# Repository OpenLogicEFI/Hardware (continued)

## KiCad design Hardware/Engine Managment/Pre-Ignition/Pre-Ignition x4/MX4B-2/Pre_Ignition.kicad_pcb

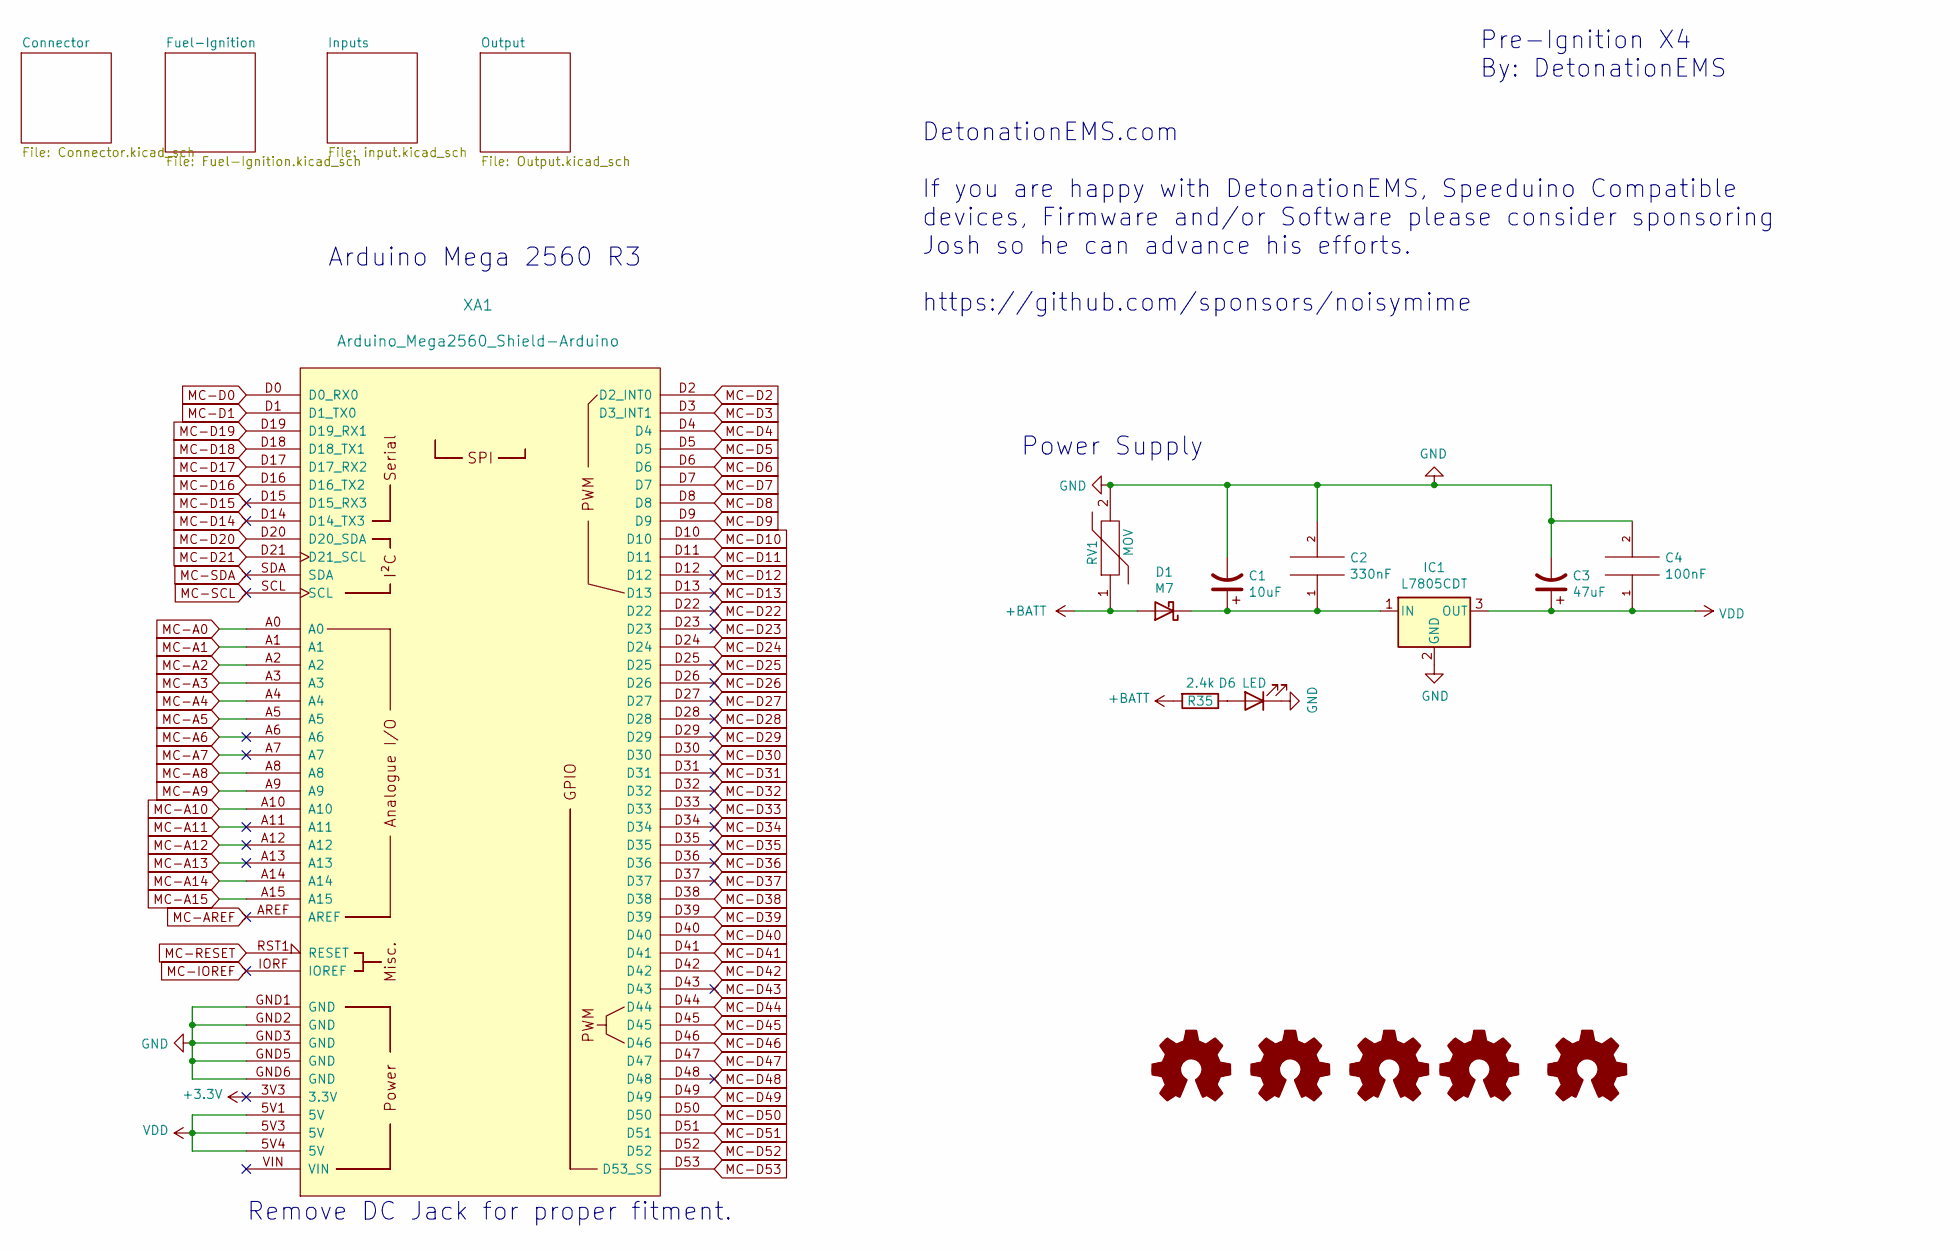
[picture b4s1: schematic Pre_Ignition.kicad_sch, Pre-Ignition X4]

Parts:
C1: 10uF; CP_Radial_Tantal_D5.0mm_P2.50mm
C2: 330nF; C_0603_1608Metric; LCSC C1615
C3: 47uF; C_1206_3216Metric; LCSC C165111
C4: 100nF; C_0603_1608Metric; LCSC C14663
D1: M7; D_SMA; LCSC C95872
D6: LED; LED_0603_1608Metric; LCSC C72043
G2: Logo_Open_Hardware_Small; TireSmoke-22mm
G3: Logo_Open_Hardware_Small; Design by DetonationEMS
G4: Logo_Open_Hardware_Small; SpeeduinoCompatible-21mm
G5: Logo_Open_Hardware_Small; Pre-IgnitionX4-30mm
G6: Logo_Open_Hardware_Small; OSHW-Logo2_14.6x12mm_SilkScreen
IC1: L7805CDT; TO-252-2-Thermal-Pad; LCSC C310413
R35: 2.4k; R_0603_1608Metric; LCSC C22940
RV1: MOV
XA1: Arduino_Mega2560_Shield-Arduino; Arduino_Mega2560_Shield_IO_Only_No_Silk_Screen

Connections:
+3V3: XA1.3V3 (3.3V)
+BATT: D1.2 (A), R35.2, RV1.1; also elsewhere on the board
Flex: XA1.D2 (D2_INT0); also elsewhere on the board
MC-A0: XA1.A0; also elsewhere on the board
MC-A1: XA1.A1; also elsewhere on the board
MC-A2: XA1.A2; also elsewhere on the board
MC-A3: XA1.A3; also elsewhere on the board
MC-A4: XA1.A4; also elsewhere on the board
MC-A5: XA1.A5; also elsewhere on the board
MC-A6: XA1.A6
MC-A7: XA1.A7
MC-A8: XA1.A8; also elsewhere on the board
MC-A9: XA1.A9; also elsewhere on the board
MC-A10: XA1.A10; also elsewhere on the board
MC-A11: XA1.A11
MC-A12: XA1.A12
MC-A13: XA1.A13
MC-A14: XA1.A14; also elsewhere on the board
MC-A15: XA1.A15; also elsewhere on the board
MC-AREF: XA1.AREF
MC-D0: XA1.D0 (D0_RX0); also elsewhere on the board
MC-D1: XA1.D1 (D1_TX0); also elsewhere on the board
MC-D3: XA1.D3 (D3_INT1)
MC-D4: XA1.D4; also elsewhere on the board
MC-D5: XA1.D5; also elsewhere on the board
MC-D6: XA1.D6; also elsewhere on the board
MC-D7: XA1.D7; also elsewhere on the board
MC-D8: XA1.D8; also elsewhere on the board
MC-D9: XA1.D9; also elsewhere on the board
MC-D10: XA1.D10; also elsewhere on the board
MC-D11: XA1.D11; also elsewhere on the board
MC-D12: XA1.D12
MC-D13: XA1.D13
MC-D14: XA1.D14 (D14_TX3)
MC-D15: XA1.D15 (D15_RX3)
MC-D16: XA1.D16 (D16_TX2); also elsewhere on the board
MC-D17: XA1.D17 (D17_RX2); also elsewhere on the board
MC-D18: XA1.D18 (D18_TX1); also elsewhere on the board
MC-D19: XA1.D19 (D19_RX1); also elsewhere on the board
MC-D20: XA1.D20 (D20_SDA); also elsewhere on the board
MC-D21: XA1.D21 (D21_SCL); also elsewhere on the board
MC-D22: XA1.D22
MC-D23: XA1.D23
MC-D24: XA1.D24; also elsewhere on the board
MC-D25: XA1.D25
MC-D26: XA1.D26
MC-D27: XA1.D27
MC-D28: XA1.D28
MC-D29: XA1.D29
MC-D30: XA1.D30
MC-D31: XA1.D31
MC-D32: XA1.D32
MC-D33: XA1.D33
MC-D34: XA1.D34
MC-D35: XA1.D35
MC-D36: XA1.D36
MC-D37: XA1.D37
MC-D38: XA1.D38; also elsewhere on the board
MC-D39: XA1.D39; also elsewhere on the board
MC-D40: XA1.D40; also elsewhere on the board
MC-D41: XA1.D41; also elsewhere on the board
MC-D42: XA1.D42; also elsewhere on the board
MC-D43: XA1.D43
MC-D44: XA1.D44; also elsewhere on the board
MC-D45: XA1.D45; also elsewhere on the board
MC-D46: XA1.D46; also elsewhere on the board
MC-D47: XA1.D47; also elsewhere on the board
MC-D48: XA1.D48
MC-D49: XA1.D49; also elsewhere on the board
MC-D50: XA1.D50; also elsewhere on the board
MC-D51: XA1.D51; also elsewhere on the board
MC-D52: XA1.D52; also elsewhere on the board
MC-D53: XA1.D53 (D53_SS); also elsewhere on the board
MC-IOREF: XA1.IORF (IOREF)
MC-RESET: XA1.RST1 (RESET); also elsewhere on the board
MC-SCL: XA1.SCL
MC-SDA: XA1.SDA
unnamed: C1.1, C2.1, D1.1 (K), IC1.1 (IN)
unnamed: D6.2 (A), R35.1

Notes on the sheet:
Remove DC Jack for proper fitment.
Pre-Ignition X4 By: DetonationEMS
DetonationEMS.com If you are happy with DetonationEMS, Speeduino Compatible devices, Firmware and/or Software please consider sponsoring Josh so he can advance his efforts. https://github.com/sponsors/noisymime
Arduino Mega 2560 R3
Power Supply

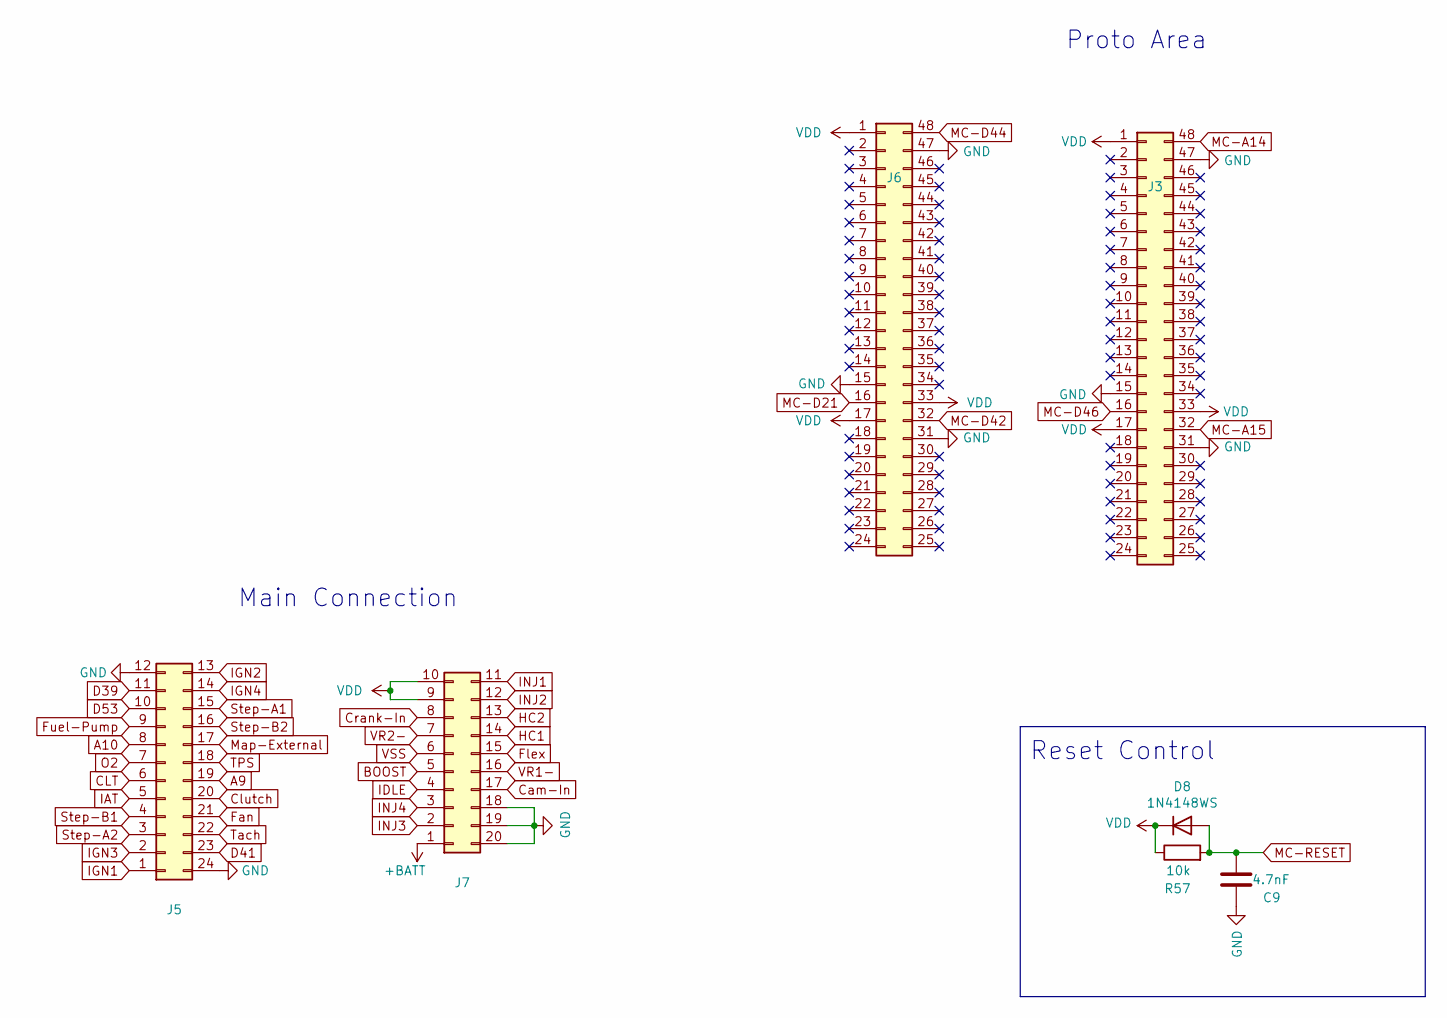
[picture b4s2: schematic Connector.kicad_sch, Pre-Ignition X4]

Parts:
C9: 4.7nF; C_0603_1608Metric; LCSC C53987
D8: 1N4148WS; D_SOD-323F; LCSC C2128
J3, J6: Conn_02x16_Counter_Clockwise; PROTO-3X16
J5: Conn_02x12_Counter_Clockwise; Molex_Micro-Fit_3.0_43045-2400_2x12_P3.00mm_Horizontal
J7: Conn_02x10_Counter_Clockwise; Molex_Micro-Fit_3.0_43045-2000_2x10_P3.00mm_Horizontal
R57: 10k; R_0603_1608Metric; LCSC C25804

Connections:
+BATT: J7.1; also elsewhere on the board
A9: J5.19; also elsewhere on the board
A10: J5.8; also elsewhere on the board
BOOST: J7.5; also elsewhere on the board
CLT: J5.6; also elsewhere on the board
Cam-In: J7.17; also elsewhere on the board
Clutch: J5.20; also elsewhere on the board
Crank-In: J7.8; also elsewhere on the board
D39: J5.11; also elsewhere on the board
D41: J5.23; also elsewhere on the board
D53: J5.10; also elsewhere on the board
Fan: J5.21; also elsewhere on the board
Flex: J7.15; also elsewhere on the board
Fuel-Pump: J5.9; also elsewhere on the board
HC1: J7.14; also elsewhere on the board
HC2: J7.13; also elsewhere on the board
IAT: J5.5; also elsewhere on the board
IDLE: J7.4; also elsewhere on the board
IGN1: J5.1; also elsewhere on the board
IGN2: J5.13; also elsewhere on the board
IGN3: J5.2; also elsewhere on the board
IGN4: J5.14; also elsewhere on the board
INJ1: J7.11; also elsewhere on the board
INJ2: J7.12; also elsewhere on the board
INJ3: J7.2; also elsewhere on the board
INJ4: J7.3; also elsewhere on the board
MC-A14: J3.48; also elsewhere on the board
MC-A15: J3.32; also elsewhere on the board
MC-D20: J7.6; also elsewhere on the board
MC-D21: J6.16; also elsewhere on the board
MC-D42: J6.32; also elsewhere on the board
MC-D44: J6.48; also elsewhere on the board
MC-D46: J3.16; also elsewhere on the board
MC-RESET: C9.2, D8.2 (A), R57.2; also elsewhere on the board
Map-External: J5.17; also elsewhere on the board
O2: J5.7; also elsewhere on the board
Step-A1: J5.15; also elsewhere on the board
Step-A2: J5.3; also elsewhere on the board
Step-B1: J5.4; also elsewhere on the board
Step-B2: J5.16; also elsewhere on the board
TPS: J5.18; also elsewhere on the board
Tach: J5.22; also elsewhere on the board
VR1-: J7.16; also elsewhere on the board
VR2-: J7.7; also elsewhere on the board

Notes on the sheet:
Reset Control
Main Connection
Proto Area

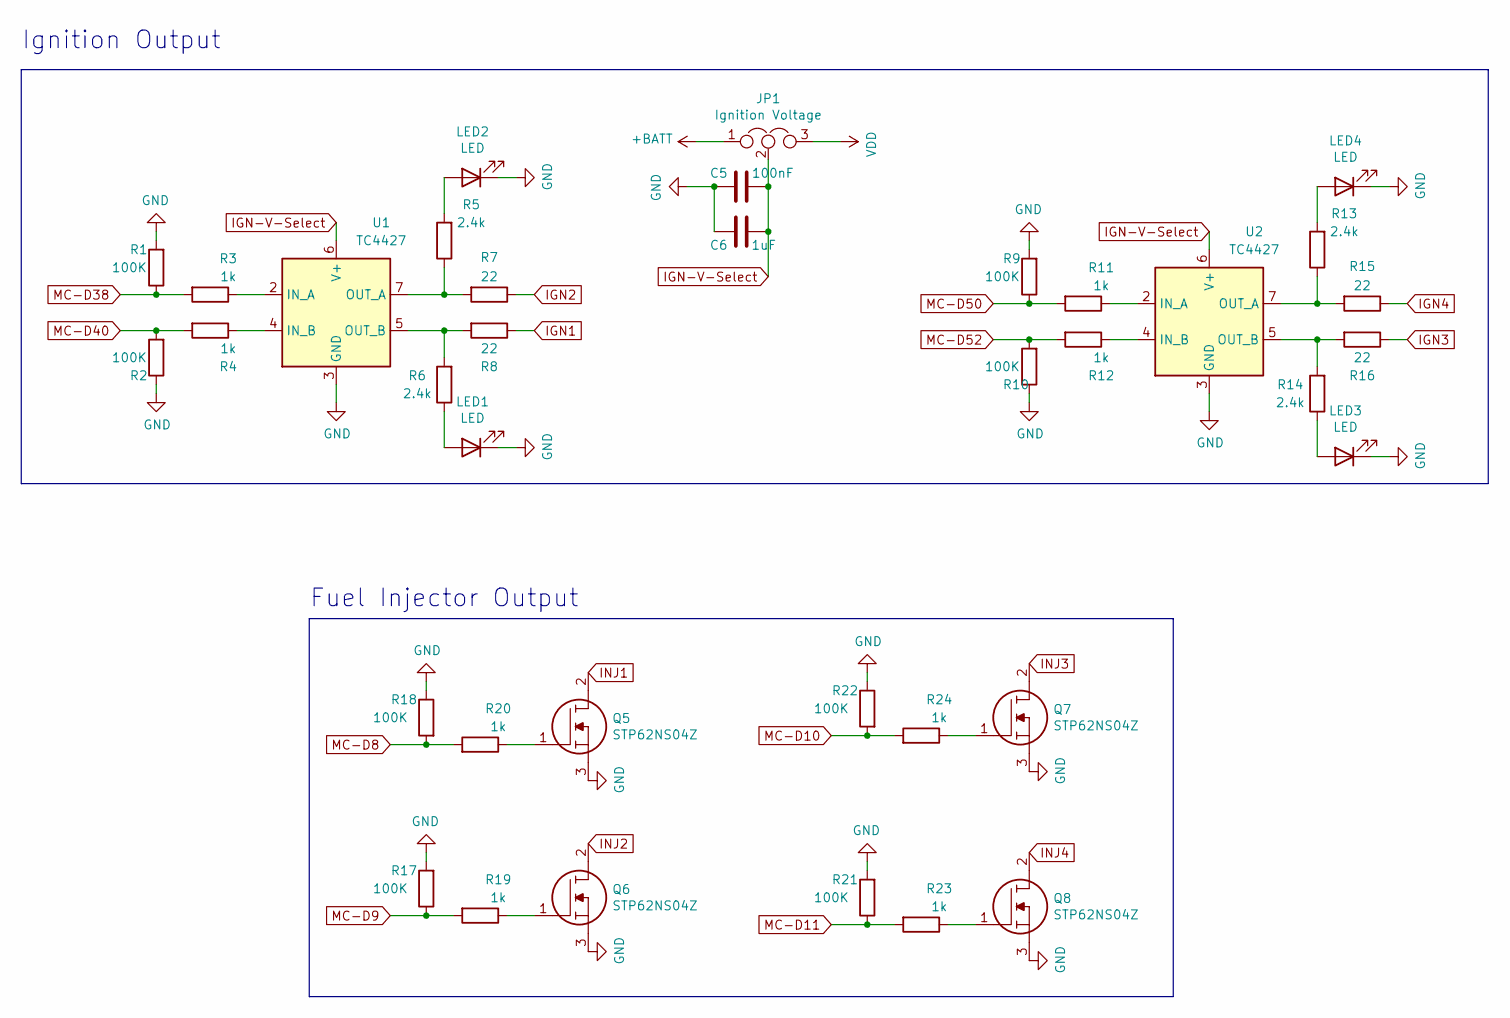
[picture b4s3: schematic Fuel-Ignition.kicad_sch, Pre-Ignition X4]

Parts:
C5: 100nF; C_0603_1608Metric; JLC C14663
C6: 1uF; C_0603_1608Metric; JLC C15849
JP1: Ignition Voltage; 3-PinSwitch
LED1, LED2, LED3, LED4: LED; LED_0603_1608Metric; JLC C2286
Q5, Q6, Q7, Q8: STP62NS04Z; TO-220-3_Vertical; Manufacturer_Part_Number STP62NS04Z; Mouser Part Number 511-STP62NS04Z
R1, R2, R9, R10, R17, R18, R21, R22: 100K; R_0603_1608Metric; JLC C25803
R3, R4, R11, R12, R19, R20, R23, R24: 1k; R_0603_1608Metric; JLC C21190
R5: 2.4k; R_0603_1608Metric; LCSC C22940
R6, R13, R14: 2.4k; R_0603_1608Metric; JLC C22940
R7, R8, R15, R16: 22; R_0805_2012Metric; JLC C17561
U1, U2: TC4427; SOIC-8_3.9x4.9mm_P1.27mm; JLC C31450

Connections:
+BATT: JP1.1; also elsewhere on the board
IGN1: R8.1; also elsewhere on the board
IGN2: R7.1; also elsewhere on the board
IGN3: R16.1; also elsewhere on the board
IGN4: R15.1; also elsewhere on the board
IGN-V-Select: C5.1, C6.1, JP1.2, U1.6 (V+), U2.6 (V+)
INJ1: Q5.2; also elsewhere on the board
INJ2: Q6.2; also elsewhere on the board
INJ3: Q7.2; also elsewhere on the board
INJ4: Q8.2; also elsewhere on the board
MC-D8: R18.2, R20.2; also elsewhere on the board
MC-D9: R17.1, R19.2; also elsewhere on the board
MC-D10: R22.2, R24.2; also elsewhere on the board
MC-D11: R21.1, R23.2; also elsewhere on the board
MC-D38: R1.1, R3.2; also elsewhere on the board
MC-D40: R2.2, R4.2; also elsewhere on the board
MC-D50: R9.1, R11.2; also elsewhere on the board
MC-D52: R10.2, R12.2; also elsewhere on the board
unnamed: LED1.2 (A), R6.1
unnamed: LED2.2 (A), R5.2
unnamed: LED3.2 (A), R14.1
unnamed: LED4.2 (A), R13.2
unnamed: Q5.1, R20.1
unnamed: Q6.1, R19.1
unnamed: Q7.1, R24.1
unnamed: Q8.1, R23.1
unnamed: R3.1, U1.2 (IN_A)
unnamed: R4.1, U1.4 (IN_B)
unnamed: R5.1, R7.2, U1.7 (OUT_A)
unnamed: R6.2, R8.2, U1.5 (OUT_B)
unnamed: R11.1, U2.2 (IN_A)
unnamed: R12.1, U2.4 (IN_B)
unnamed: R13.1, R15.2, U2.7 (OUT_A)
unnamed: R14.2, R16.2, U2.5 (OUT_B)

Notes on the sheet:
Ignition Output
Fuel Injector Output

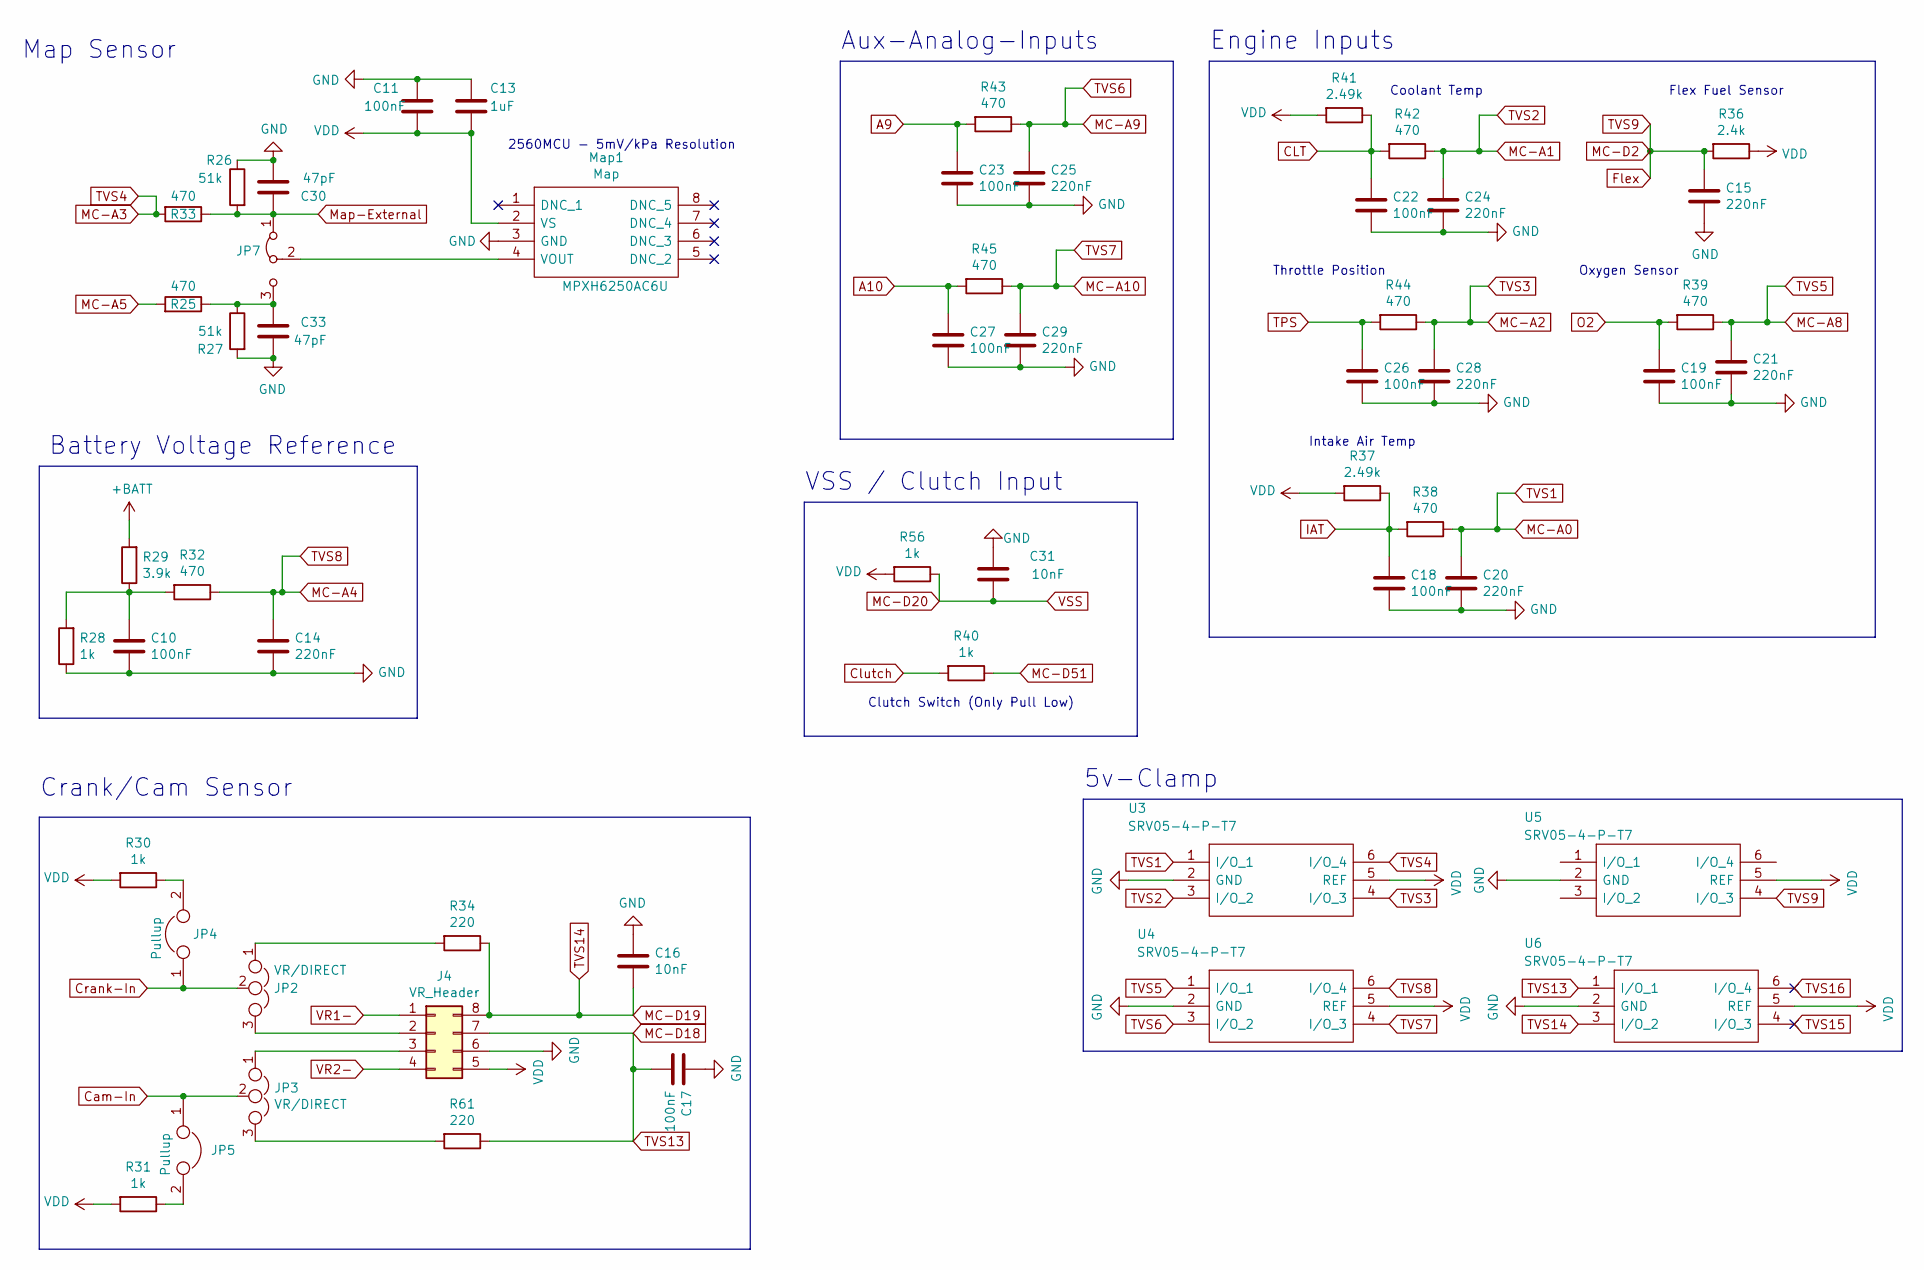
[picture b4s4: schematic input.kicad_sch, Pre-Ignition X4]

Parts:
C10, C11, C17, C18, C19, C22, C23, C26, C27: 100nF; C_0603_1608Metric; JLC C14663
C13: 1uF; C_0603_1608Metric; JLC C15849
C14, C15, C20, C21, C24, C25, C28, C29: 220nF; C_0603_1608Metric; JLC C5378
C16, C31: 10nF; C_0603_1608Metric; JLC C57112
C30, C33: 47pF; C_0603_1608Metric; LCSC C1671
J4: VR_Header; Socket_VRConditioner
JP2, JP3: VR/DIRECT; 3x1-GPIO
JP4, JP5: Pullup; 1x02-Proto
JP7: Jumper_3_Bridged12; 3-PinSwitch
Map1: Map; Freescale_98ARH99066A; Manufacturer_Part_Number MPXH6250AC6U; Mouser Part Number 841-MPXH6250AC6U
R25, R32, R33, R38, R39, R42, R43, R44, R45: 470; R_0603_1608Metric; JLC C23179
R26, R27: 51k; R_0603_1608Metric; JLC C23196
R28, R30, R31, R40, R56: 1k; R_0603_1608Metric; JLC C21190
R29: 3.9k; R_0603_1608Metric; JLC C23018
R34, R61: 220; R_0603_1608Metric; LCSC C22962
R36: 2.4k; R_0603_1608Metric; JLC C22940
R37, R41: 2.49k; R_0603_1608Metric; LCSC C491121
U3, U4, U5, U6: SRV05-4-P-T7; SOT-23-6; JLC C85364

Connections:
+BATT: R29.2; also elsewhere on the board
A9: C23.1, R43.2; also elsewhere on the board
A10: C27.1, R45.2; also elsewhere on the board
CLT: C22.1, R41.1, R42.2; also elsewhere on the board
Cam-In: JP3.2, JP5.1; also elsewhere on the board
Clutch: R40.2; also elsewhere on the board
Crank-In: JP2.2, JP4.1; also elsewhere on the board
Flex: C15.1, R36.2, U5.4 (I/O_3); also elsewhere on the board
IAT: C18.1, R37.1, R38.2; also elsewhere on the board
MC-A0: C20.1, R38.1, U3.1 (I/O_1); also elsewhere on the board
MC-A1: C24.1, R42.1, U3.3 (I/O_2); also elsewhere on the board
MC-A2: C28.1, R44.1, U3.4 (I/O_3); also elsewhere on the board
MC-A3: R33.2, U3.6 (I/O_4); also elsewhere on the board
MC-A4: C14.1, R32.1, U4.6 (I/O_4); also elsewhere on the board
MC-A5: R25.2; also elsewhere on the board
MC-A8: C21.1, R39.1, U4.1 (I/O_1); also elsewhere on the board
MC-A9: C25.1, R43.1, U4.3 (I/O_2); also elsewhere on the board
MC-A10: C29.1, R45.1, U4.4 (I/O_3); also elsewhere on the board
MC-D18: C17.2, J4.7, R61.1, U6.1 (I/O_1); also elsewhere on the board
MC-D19: C16.2, J4.8, R34.1, U6.3 (I/O_2); also elsewhere on the board
MC-D20: C31.1, R56.1; also elsewhere on the board
MC-D51: R40.1; also elsewhere on the board
Map-External: C30.1, JP7.1 (A), R26.2, R33.1; also elsewhere on the board
unnamed: C10.1, R28.2, R29.1, R32.2
unnamed: C33.1, JP7.3 (B), R25.1, R27.1
unnamed: J4.2, JP2.3
unnamed: J4.3, JP3.1
unnamed: JP2.1, R34.2
unnamed: JP3.3, R61.2
unnamed: JP4.2, R30.1
unnamed: JP5.2, R31.1
unnamed: JP7.2 (C), Map1.4 (VOUT)
O2: C19.1, R39.2; also elsewhere on the board
TPS: C26.1, R44.2; also elsewhere on the board
TVS15: U6.4 (I/O_3)
TVS16: U6.6 (I/O_4)
VR1-: J4.1; also elsewhere on the board
VR2-: J4.4; also elsewhere on the board

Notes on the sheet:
2560MCU - 5mV/kPa Resolution
Coolant Temp
Throttle Position
VSS / Clutch Input
Intake Air Temp
Battery Voltage Reference
Crank/Cam Sensor
Map Sensor
Engine Inputs
Clutch Switch (Only Pull Low)
Aux-Analog-Inputs
Flex Fuel Sensor
Oxygen Sensor
5v-Clamp

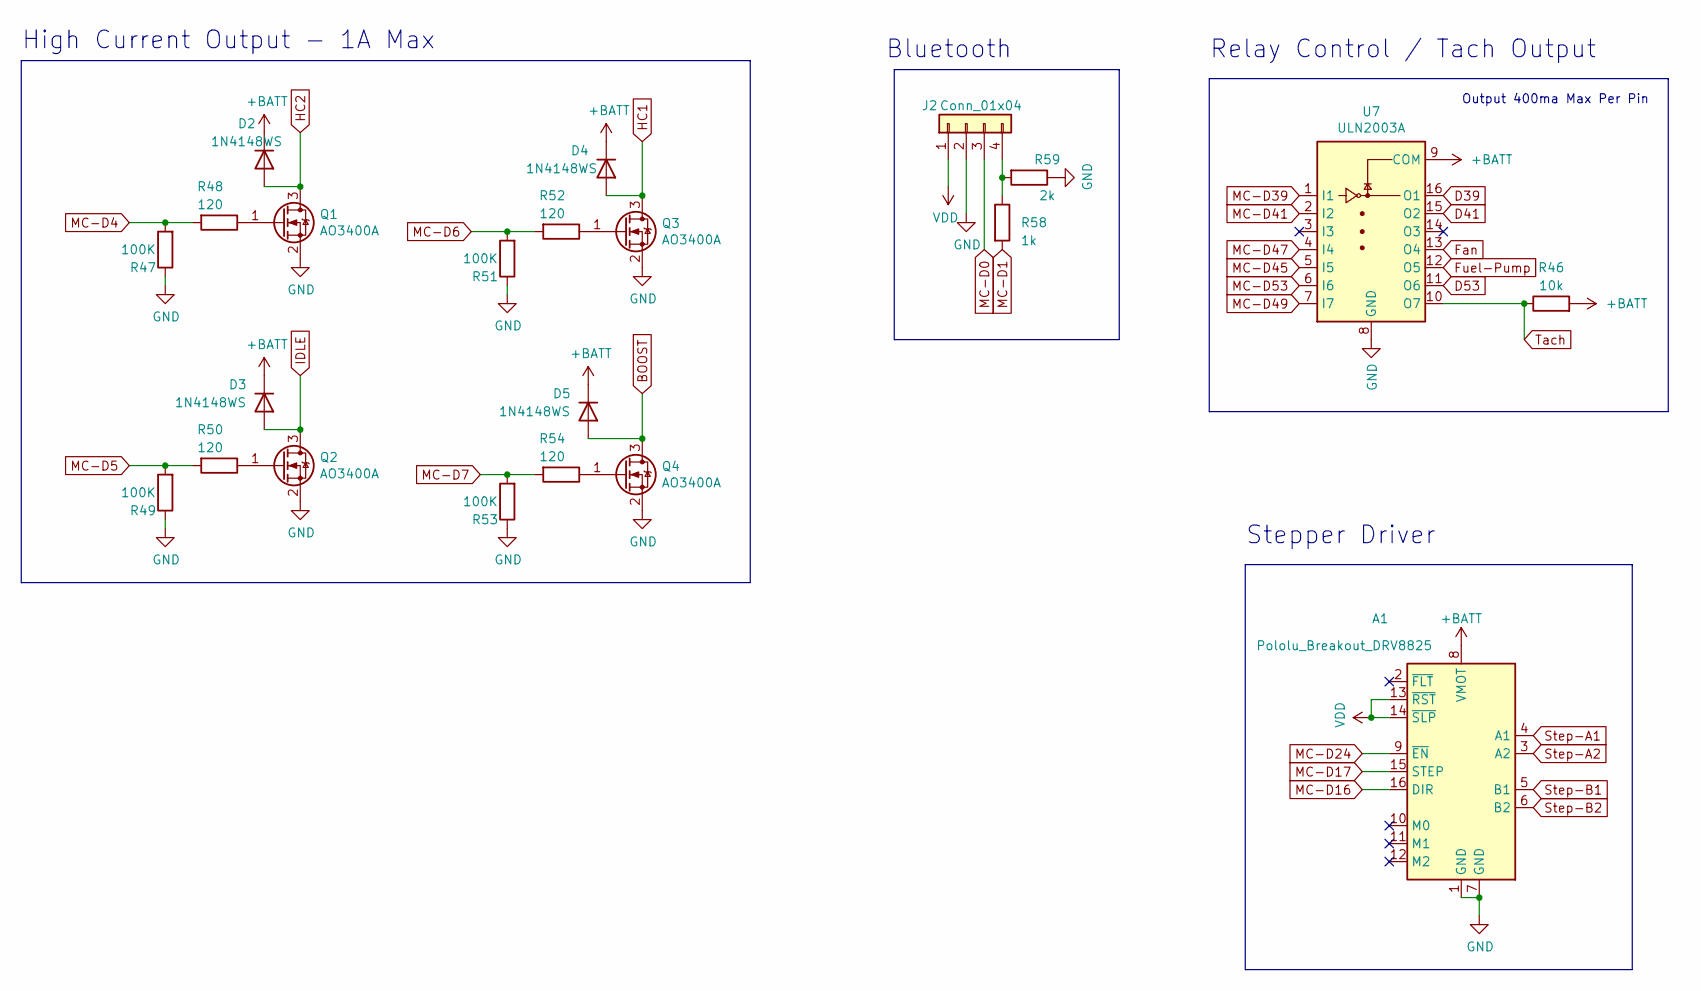
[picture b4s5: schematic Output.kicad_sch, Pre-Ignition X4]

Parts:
A1: Pololu_Breakout_DRV8825; Pololu_Breakout-16_15.2x20.3mm
D2, D3, D4, D5: 1N4148WS; D_SOD-323F; JLC C2128
J2: Conn_01x04; 1X4-PROTO
Q1, Q2, Q3, Q4: AO3400A; SOT-23; JLC C20917
R46: 10k; R_0603_1608Metric; JLC C25804
R47, R49, R51, R53: 100K; R_0603_1608Metric; LCSC C25803
R48, R50, R52, R54: 120; R_0603_1608Metric; LCSC C22787
R58: 1k; R_0603_1608Metric; LCSC C21190
R59: 2k; R_0603_1608Metric; LCSC C22975
U7: ULN2003A; SOIC-16_3.9x9.9mm_P1.27mm; JLC C7512

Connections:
+BATT: A1.8 (VMOT), D2.1 (K), D3.1 (K), D4.1 (K), D5.1 (K), R46.2, U7.9 (COM); also elsewhere on the board
BOOST: D5.2 (A), Q4.3 (D); also elsewhere on the board
D39: U7.16 (O1); also elsewhere on the board
D41: U7.15 (O2); also elsewhere on the board
D53: U7.11 (O6); also elsewhere on the board
Fan: U7.13 (O4); also elsewhere on the board
Fuel-Pump: U7.12 (O5); also elsewhere on the board
HC1: D4.2 (A), Q3.3 (D); also elsewhere on the board
HC2: D2.2 (A), Q1.3 (D); also elsewhere on the board
IDLE: D3.2 (A), Q2.3 (D); also elsewhere on the board
MC-D0: J2.3; also elsewhere on the board
MC-D1: R58.2; also elsewhere on the board
MC-D4: R47.2, R48.2; also elsewhere on the board
MC-D5: R49.2, R50.2; also elsewhere on the board
MC-D6: R51.2, R52.2; also elsewhere on the board
MC-D7: R53.2, R54.2; also elsewhere on the board
MC-D16: A1.16 (DIR); also elsewhere on the board
MC-D17: A1.15 (STEP); also elsewhere on the board
MC-D24: A1.9 (~EN); also elsewhere on the board
MC-D39: U7.1 (I1); also elsewhere on the board
MC-D41: U7.2 (I2); also elsewhere on the board
MC-D45: U7.5 (I5); also elsewhere on the board
MC-D47: U7.4 (I4); also elsewhere on the board
MC-D49: U7.7 (I7); also elsewhere on the board
MC-D53: U7.6 (I6); also elsewhere on the board
unnamed: J2.4, R58.1, R59.2
unnamed: Q1.1 (G), R48.1
unnamed: Q2.1 (G), R50.1
unnamed: Q3.1 (G), R52.1
unnamed: Q4.1 (G), R54.1
Step-A1: A1.4 (A1); also elsewhere on the board
Step-A2: A1.3 (A2); also elsewhere on the board
Step-B1: A1.5 (B1); also elsewhere on the board
Step-B2: A1.6 (B2); also elsewhere on the board
Tach: R46.1, U7.10 (O7); also elsewhere on the board

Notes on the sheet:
Bluetooth
High Current Output - 1A Max
Relay Control / Tach Output
Stepper Driver
Output 400ma Max Per Pin

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
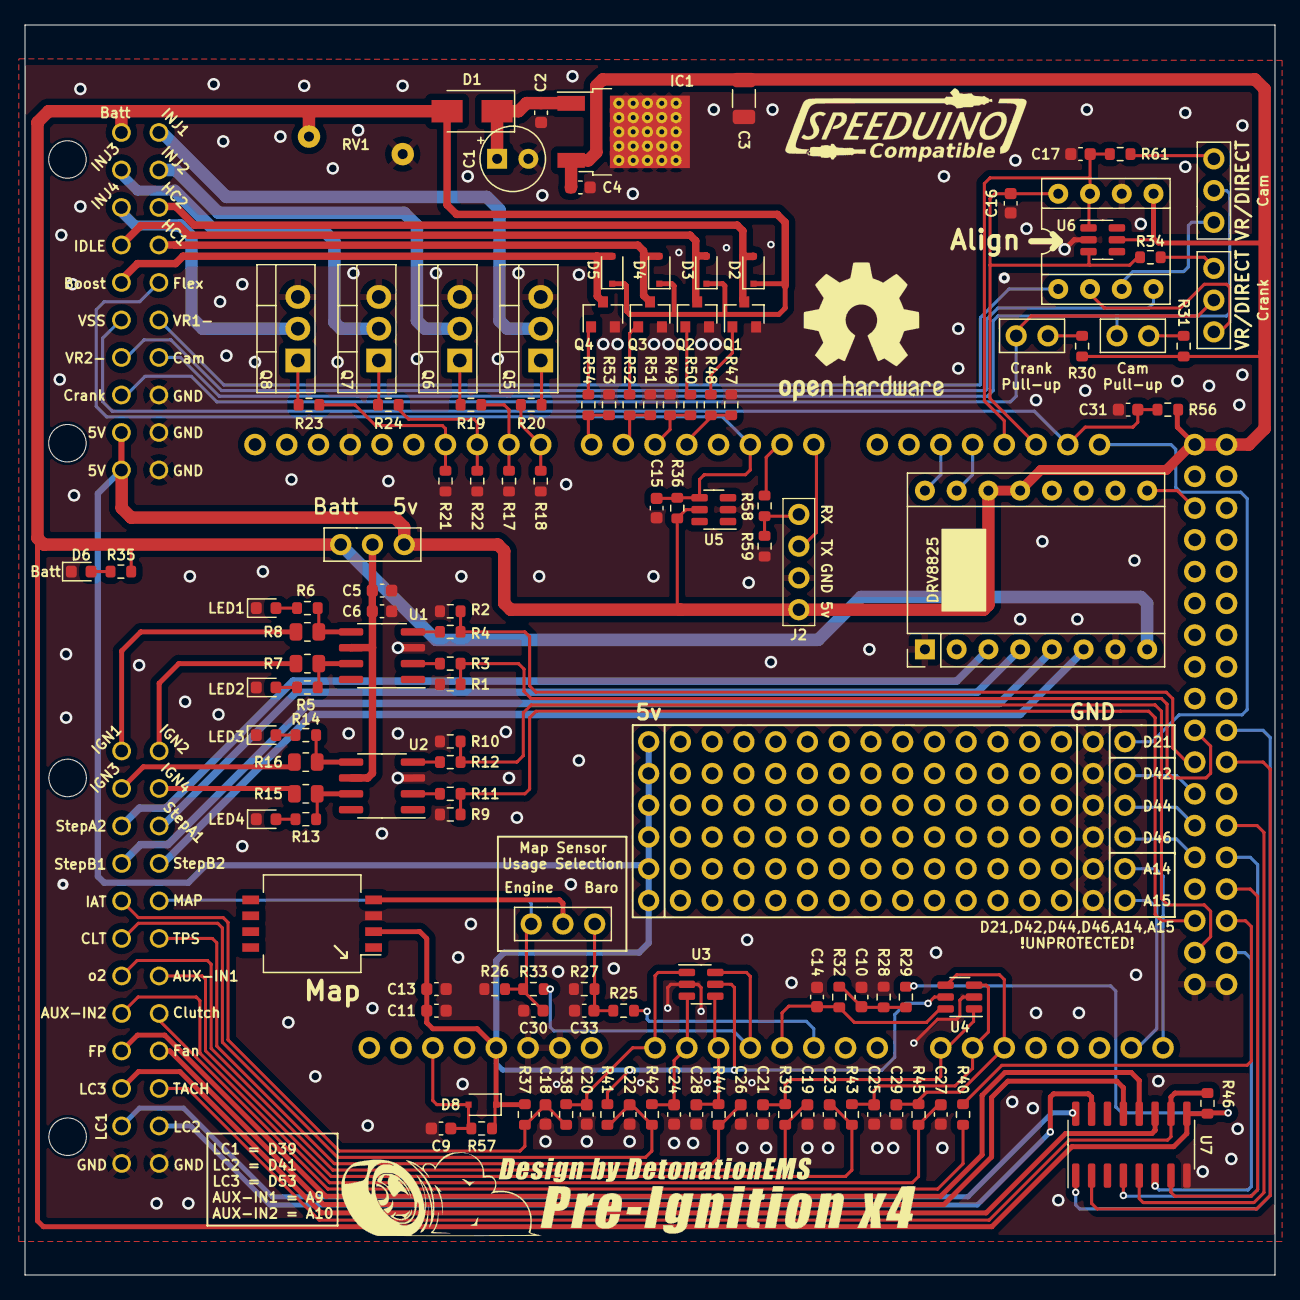
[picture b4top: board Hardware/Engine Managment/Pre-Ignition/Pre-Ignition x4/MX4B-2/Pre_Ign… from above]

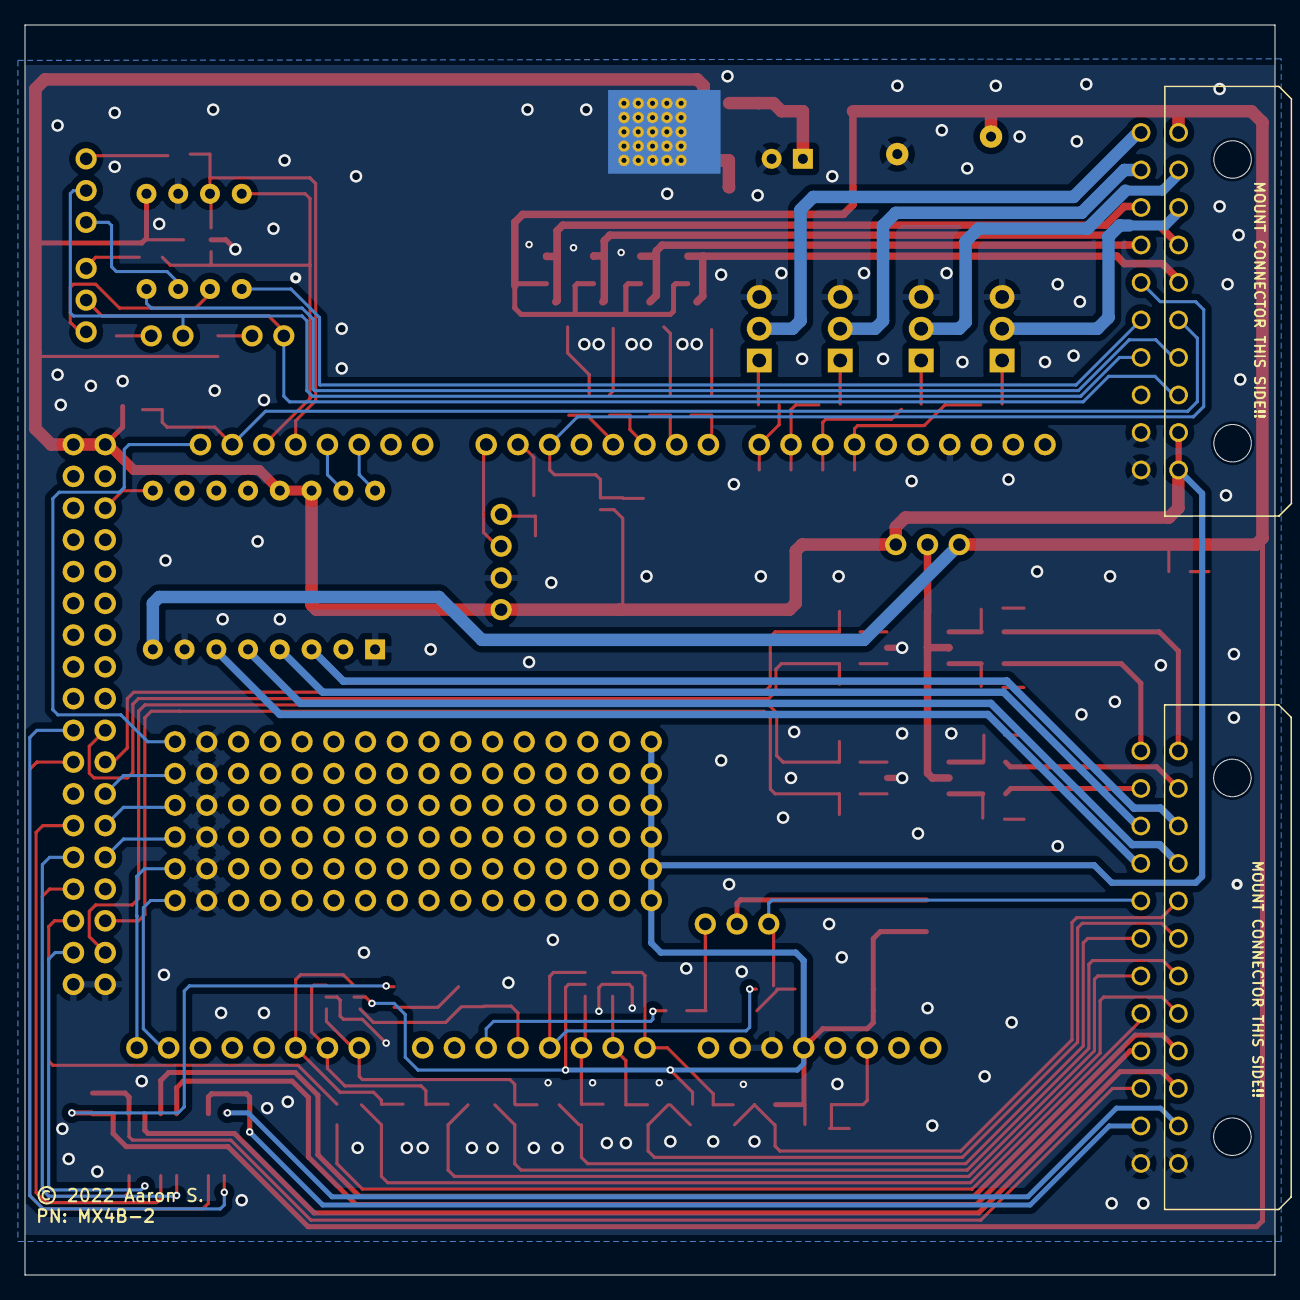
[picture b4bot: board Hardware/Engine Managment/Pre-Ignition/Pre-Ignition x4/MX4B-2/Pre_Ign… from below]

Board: 2 copper layers, 100.0 x 100.0 mm, 136 parts (2 on the bottom side), 114 nets.

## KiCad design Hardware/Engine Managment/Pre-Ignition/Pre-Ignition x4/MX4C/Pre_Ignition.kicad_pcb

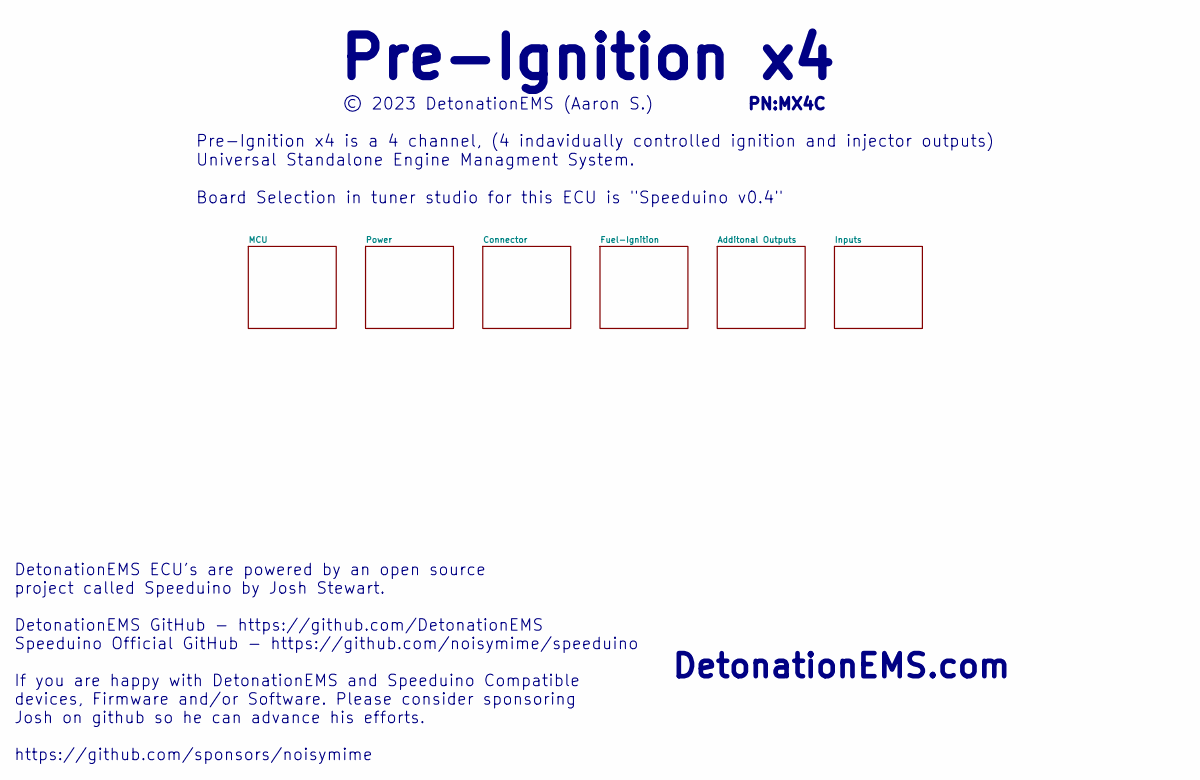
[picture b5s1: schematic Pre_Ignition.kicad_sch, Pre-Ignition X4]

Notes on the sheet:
Pre-Ignition x4 is a 4 channel, (4 indavidually controlled ignition and injector outputs) Universal Standalone Engine Managment System. Board Selection in tuner studio for this ECU is "Speeduino v0.4"
© 2023 DetonationEMS (Aaron S.)
Pre-Ignition x4
DetonationEMS.com
DetonationEMS ECU's are powered by an open source project called Speeduino by Josh Stewart. DetonationEMS GitHub - https://github.com/DetonationEMS Speeduino Official GitHub - https://github.com/noisymime/speeduino If you are happy with DetonationEMS and Speeduino Compatible devices, Firmware and/o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
PN:MX4C
